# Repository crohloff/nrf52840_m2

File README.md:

# nrf52840_m2
nrf52840 based M.2 b-key module

## dimensions
- 22mm x 30mm

## features
- m.2 2230 b-key form factor board
- dedicated smd chip antenna for bt
- U.fl connector for NFC antenna
- TC2030 debug connector
- RGB led
- power path management (USB or battery connected)
- battery charging circuit 500mA charging current
- up to 24 free programmable GPIOs(4 analog) without expensive uVias

## board front

## board back

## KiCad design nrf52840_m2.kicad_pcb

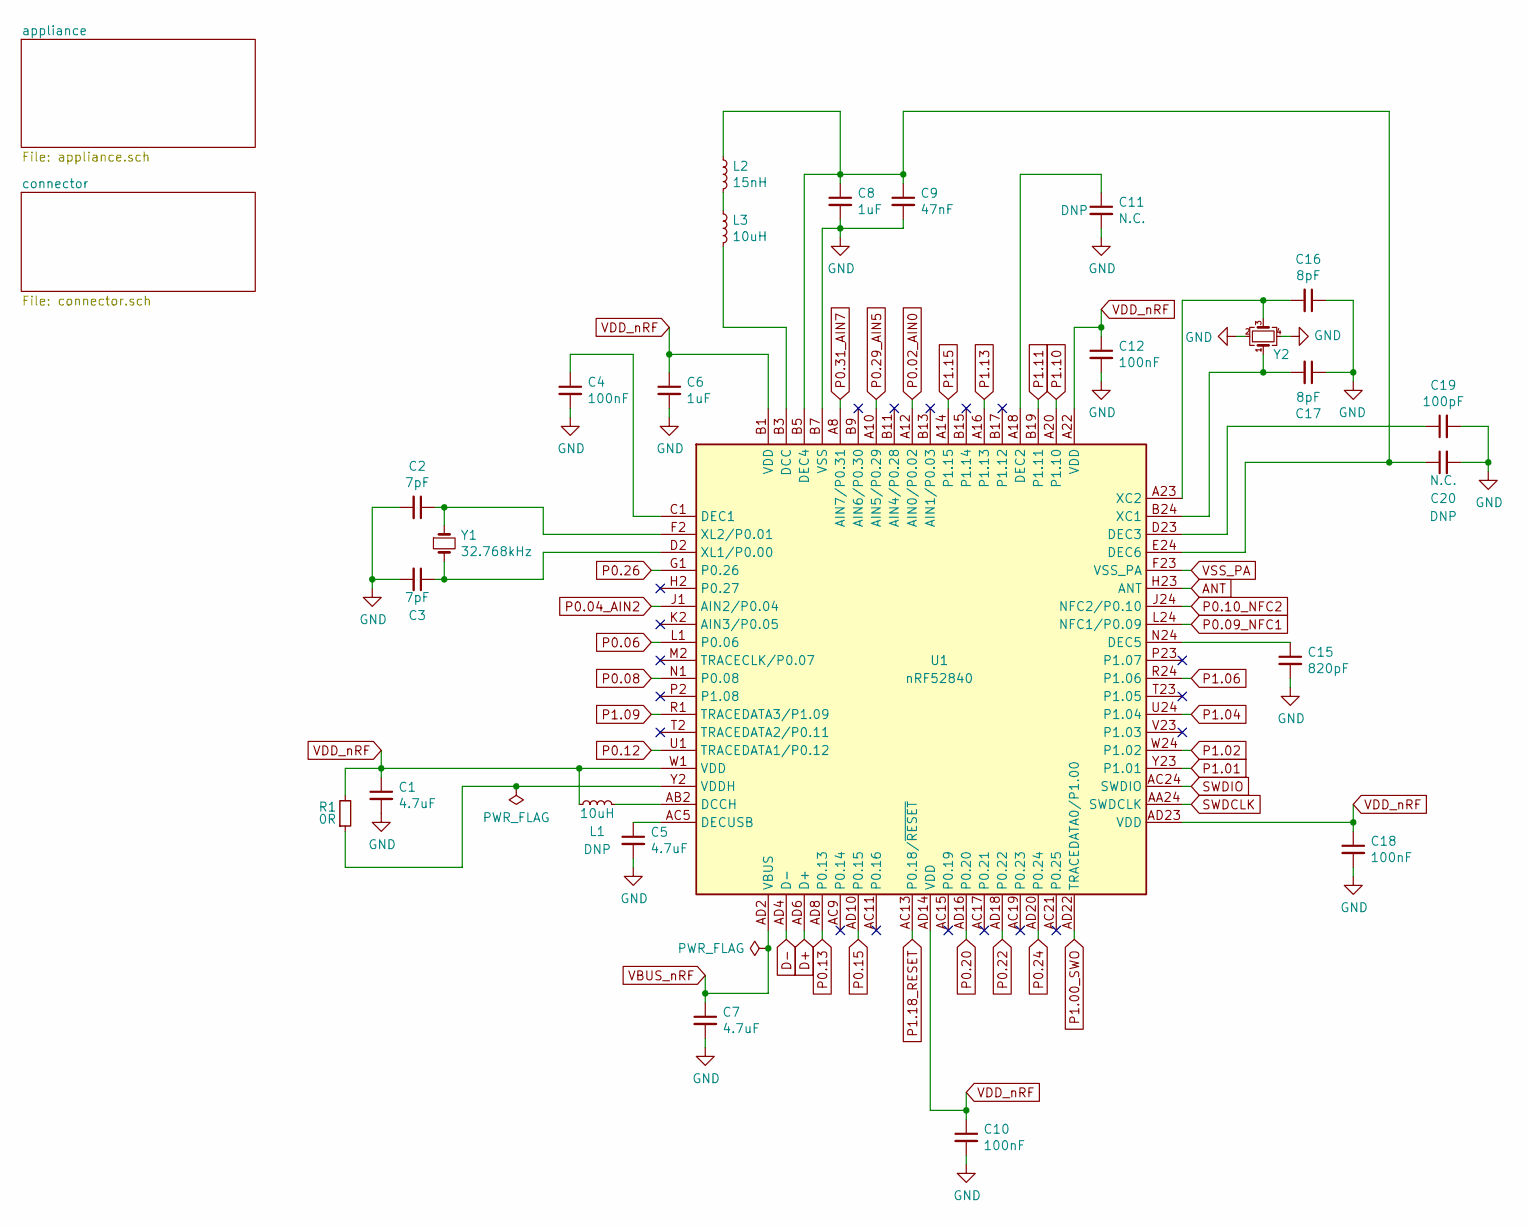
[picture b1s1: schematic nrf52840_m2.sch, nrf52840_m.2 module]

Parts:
C1, C5, C7: 4.7uF; C_0402_1005Metric; MFG P/N JMK105BBJ475MV-F; Digikey 587-2787-1-ND
C2, C3: 7pF; C_0402_1005Metric; MFG P/N GRM1555C1H7R0BA01D; Digikey 490-6254-1-ND
C4, C10, C12, C18: 100nF; C_0402_1005Metric; MFG P/N CL05A104KP5NNNC; Digikey 1276-1022-1-ND
C6, C8: 1uF; C_0402_1005Metric; MFG P/N CL05A105KO5NNNC; Digikey 1276-1067-1-ND
C9: 47nF; C_0402_1005Metric; MFG P/N CC0402KRX7R9BB473; Digikey 311-3815-1-ND
C11, C20: N.C.; C_0402_1005Metric
C15: 820pF; C_0402_1005Metric; MFG P/N CL05B821KB5NNNC; Digikey 1276-1589-1-ND
C16, C17: 8pF; C_0402_1005Metric; MFG P/N CC0402CRNPO9BN8R0; Digikey 311-3328-1-ND
C19: 100pF; C_0402_1005Metric; MFG P/N CC0402JRNPO9BN101; Digikey 311-1024-1-ND
L1, L3: 10uH; L_0603_1608Metric; MFG P/N LQM18FN100M00D; Digikey 490-4025-1-ND
L2: 15nH; L_0402_1005Metric; MFG P/N LQW15AN15NG00D; Digikey 490-6771-1-ND
R1: 0R; R_0402_1005Metric; MFG P/N RC0402JR-070RL; Digikey 311-0.0JRCT-ND
U1: nRF52840; Nordic_AQFN-73-1EP_7x7mm_P0.5mm; MFG P/N NRF52840-QIAA-R; Digikey 1490-1071-1-ND
Y1: 32.768kHz; Crystal_SMD_2012-2Pin_2.0x1.2mm; MFG P/N SC20S-7PF20PPM; Digikey 728-1076-1-ND
Y2: 32MHz; Crystal_SMD_2016-4Pin_2.0x1.6mm; MFG P/N X201632MKD4SI; LCSC C108165

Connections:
ANT: U1.H23 (ANT); also elsewhere on the board
D+: U1.AD6 (D+); also elsewhere on the board
D-: U1.AD4 (D-); also elsewhere on the board
unnamed: C2.1, U1.F2 (XL2/P0.01), Y1.1
unnamed: C3.1, U1.D2 (XL1/P0.00), Y1.2
unnamed: C4.1, U1.C1 (DEC1)
unnamed: C5.1, U1.AC5 (DECUSB)
unnamed: C11.1, U1.A18 (DEC2)
unnamed: C15.1, U1.N24 (DEC5)
unnamed: C16.2, U1.A23 (XC2), Y2.3
unnamed: C17.2, U1.B24 (XC1), Y2.1
unnamed: C19.1, U1.D23 (DEC3)
unnamed: C8.1, C9.1, C20.1, L2.1, U1.B5 (DEC4), U1.E24 (DEC6)
unnamed: L1.2, U1.AB2 (DCCH)
unnamed: L2.2, L3.1
unnamed: L3.2, U1.B3 (DCC)
unnamed: R1.1, U1.Y2 (VDDH)
P0.02_AIN0: U1.A12 (AIN0/P0.02); also elsewhere on the board
P0.04_AIN2: U1.J1 (AIN2/P0.04); also elsewhere on the board
P0.06: U1.L1 (P0.06); also elsewhere on the board
P0.08: U1.N1 (P0.08); also elsewhere on the board
P0.09_NFC1: U1.L24 (NFC1/P0.09); also elsewhere on the board
P0.10_NFC2: U1.J24 (NFC2/P0.10); also elsewhere on the board
P0.12: U1.U1 (TRACEDATA1/P0.12); also elsewhere on the board
P0.13: U1.AD8 (P0.13); also elsewhere on the board
P0.15: U1.AD10 (P0.15); also elsewhere on the board
P0.20: U1.AD16 (P0.20); also elsewhere on the board
P0.22: U1.AD18 (P0.22); also elsewhere on the board
P0.24: U1.AD20 (P0.24); also elsewhere on the board
P0.26: U1.G1 (P0.26); also elsewhere on the board
P0.29_AIN5: U1.A10 (AIN5/P0.29); also elsewhere on the board
P0.31_AIN7: U1.A8 (AIN7/P0.31); also elsewhere on the board
P1.00_SWO: U1.AD22 (TRACEDATA0/P1.00); also elsewhere on the board
P1.01: U1.Y23 (P1.01); also elsewhere on the board
P1.02: U1.W24 (P1.02); also elsewhere on the board
P1.04: U1.U24 (P1.04); also elsewhere on the board
P1.06: U1.R24 (P1.06); also elsewhere on the board
P1.09: U1.R1 (TRACEDATA3/P1.09); also elsewhere on the board
P1.10: U1.A20 (P1.10); also elsewhere on the board
P1.11: U1.B19 (P1.11); also elsewhere on the board
P1.13: U1.A16 (P1.13); also elsewhere on the board
P1.15: U1.A14 (P1.15); also elsewhere on the board
P1.18_RESET: U1.AC13 (P0.18/~RESET); also elsewhere on the board
SWDCLK: U1.AA24 (SWDCLK); also elsewhere on the board
SWDIO: U1.AC24 (SWDIO); also elsewhere on the board
VBUS_nRF: C7.1, U1.AD2 (VBUS); also elsewhere on the board
VDD_nRF: C1.1, C6.1, C10.1, C12.1, C18.1, L1.1, R1.2, U1.A22 (VDD), U1.AD14 (VDD), U1.AD23 (VDD), U1.B1 (VDD), U1.W1 (VDD); also elsewhere on the board
VSS_PA: C1.2, C2.2, C3.2, C4.2, C5.2, C6.2, C7.2, C8.2, C9.2, C10.2, C11.2, C12.2, C15.2, C16.1, C17.1, C18.2, C19.2, C20.2, U1.B7 (VSS), U1.EP (VSS), U1.F23 (VSS_PA), Y2.2, Y2.4; also elsewhere on the board

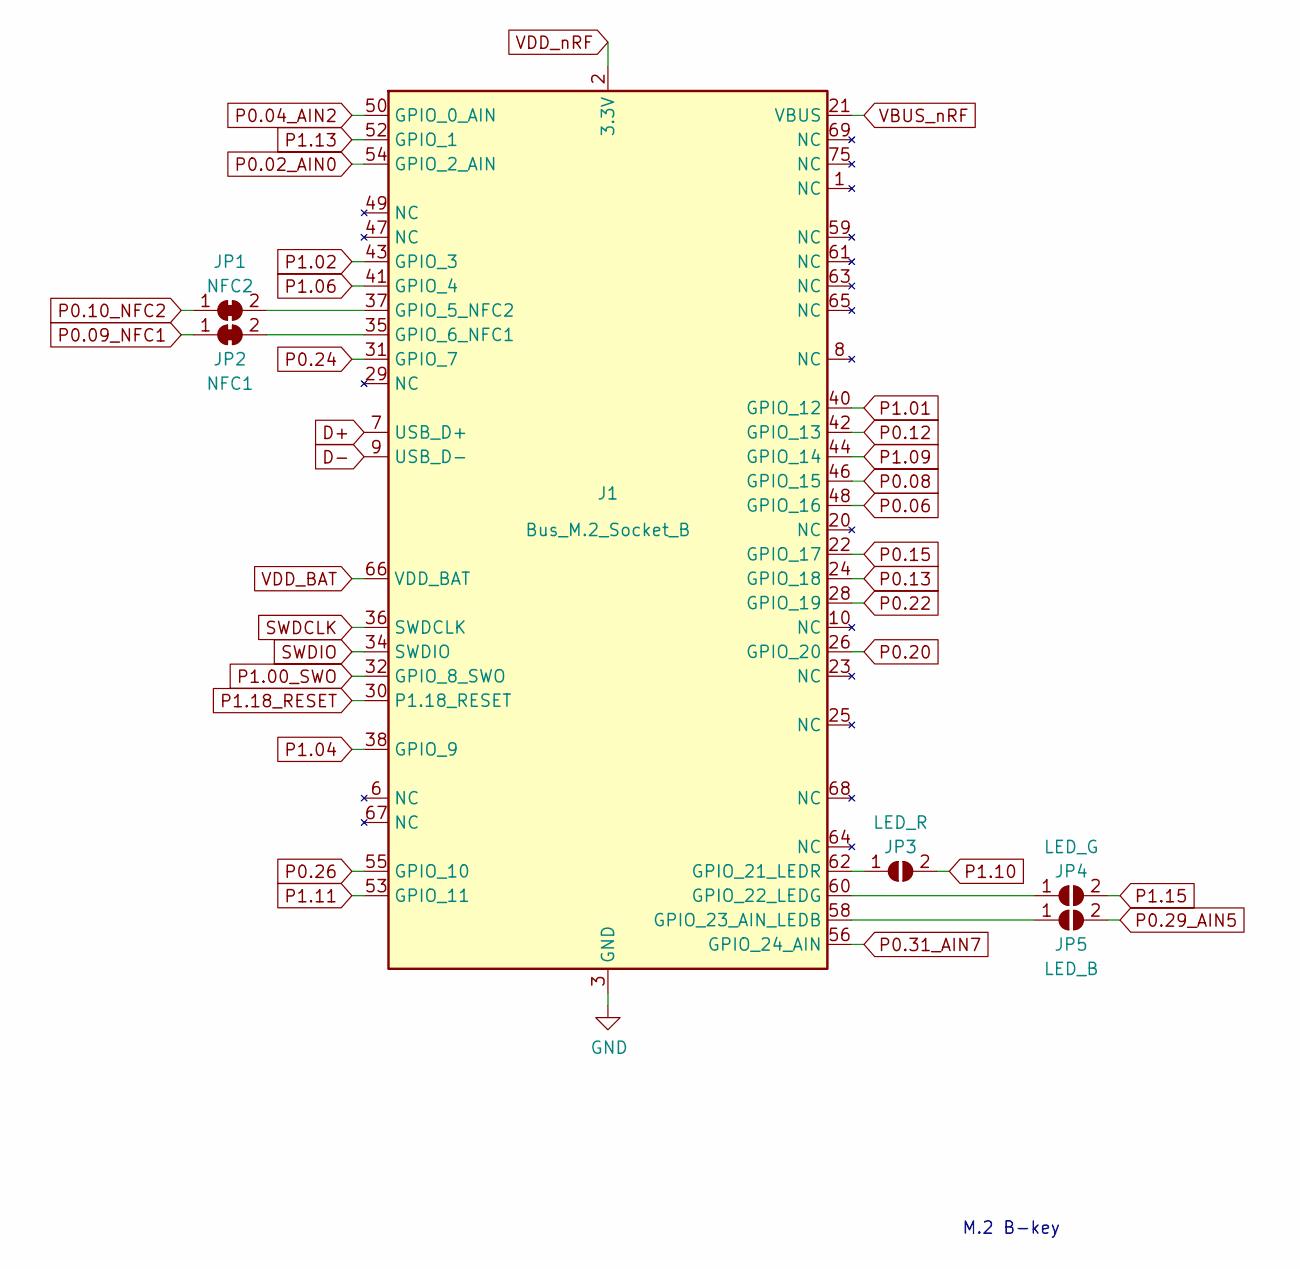
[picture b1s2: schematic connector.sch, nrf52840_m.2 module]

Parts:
J1: Bus_M.2_Socket_B; NGFF_B
JP1: NFC2; solder_bridge_closed
JP2: NFC1; solder_bridge_closed
JP3: LED_R; solder_bridge_open
JP4: LED_G; solder_bridge_open
JP5: LED_B; solder_bridge_open

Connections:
D+: J1.7 (USB_D+); also elsewhere on the board
D-: J1.9 (USB_D-); also elsewhere on the board
unnamed: J1.35 (GPIO_6_NFC1), JP2.2 (B)
unnamed: J1.37 (GPIO_5_NFC2), JP1.2 (B)
unnamed: J1.58 (GPIO_23_AIN_LEDB), JP5.1 (A)
unnamed: J1.60 (GPIO_22_LEDG), JP4.1 (A)
unnamed: J1.62 (GPIO_21_LEDR), JP3.1 (A)
P0.02_AIN0: J1.54 (GPIO_2_AIN); also elsewhere on the board
P0.04_AIN2: J1.50 (GPIO_0_AIN); also elsewhere on the board
P0.06: J1.48 (GPIO_16); also elsewhere on the board
P0.08: J1.46 (GPIO_15); also elsewhere on the board
P0.09_NFC1: JP2.1 (A); also elsewhere on the board
P0.10_NFC2: JP1.1 (A); also elsewhere on the board
P0.12: J1.42 (GPIO_13); also elsewhere on the board
P0.13: J1.24 (GPIO_18); also elsewhere on the board
P0.15: J1.22 (GPIO_17); also elsewhere on the board
P0.20: J1.26 (GPIO_20); also elsewhere on the board
P0.22: J1.28 (GPIO_19); also elsewhere on the board
P0.24: J1.31 (GPIO_7); also elsewhere on the board
P0.26: J1.55 (GPIO_10); also elsewhere on the board
P0.29_AIN5: JP5.2 (B); also elsewhere on the board
P0.31_AIN7: J1.56 (GPIO_24_AIN); also elsewhere on the board
P1.00_SWO: J1.32 (GPIO_8_SWO); also elsewhere on the board
P1.01: J1.40 (GPIO_12); also elsewhere on the board
P1.02: J1.43 (GPIO_3); also elsewhere on the board
P1.04: J1.38 (GPIO_9); also elsewhere on the board
P1.06: J1.41 (GPIO_4); also elsewhere on the board
P1.09: J1.44 (GPIO_14); also elsewhere on the board
P1.10: JP3.2 (B); also elsewhere on the board
P1.11: J1.53 (GPIO_11); also elsewhere on the board
P1.13: J1.52 (GPIO_1); also elsewhere on the board
P1.15: JP4.2 (B); also elsewhere on the board
P1.18_RESET: J1.30 (P1.18_RESET); also elsewhere on the board
SWDCLK: J1.36 (SWDCLK); also elsewhere on the board
SWDIO: J1.34 (SWDIO); also elsewhere on the board
VBUS_nRF: J1.21 (VBUS); also elsewhere on the board
VDD_BAT: J1.66 (VDD_BAT); also elsewhere on the board
VDD_nRF: J1.2 (3.3V), J1.4 (3.3V), J1.70 (3.3V), J1.72 (3.3V), J1.74 (3.3V); also elsewhere on the board
VSS_PA: J1.3 (GND), J1.5 (GND), J1.11 (GND), J1.27 (GND), J1.33 (GND), J1.39 (GND), J1.45 (GND), J1.51 (GND), J1.57 (GND), J1.71 (GND), J1.73 (GND); also elsewhere on the board

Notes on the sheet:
M.2 B-key

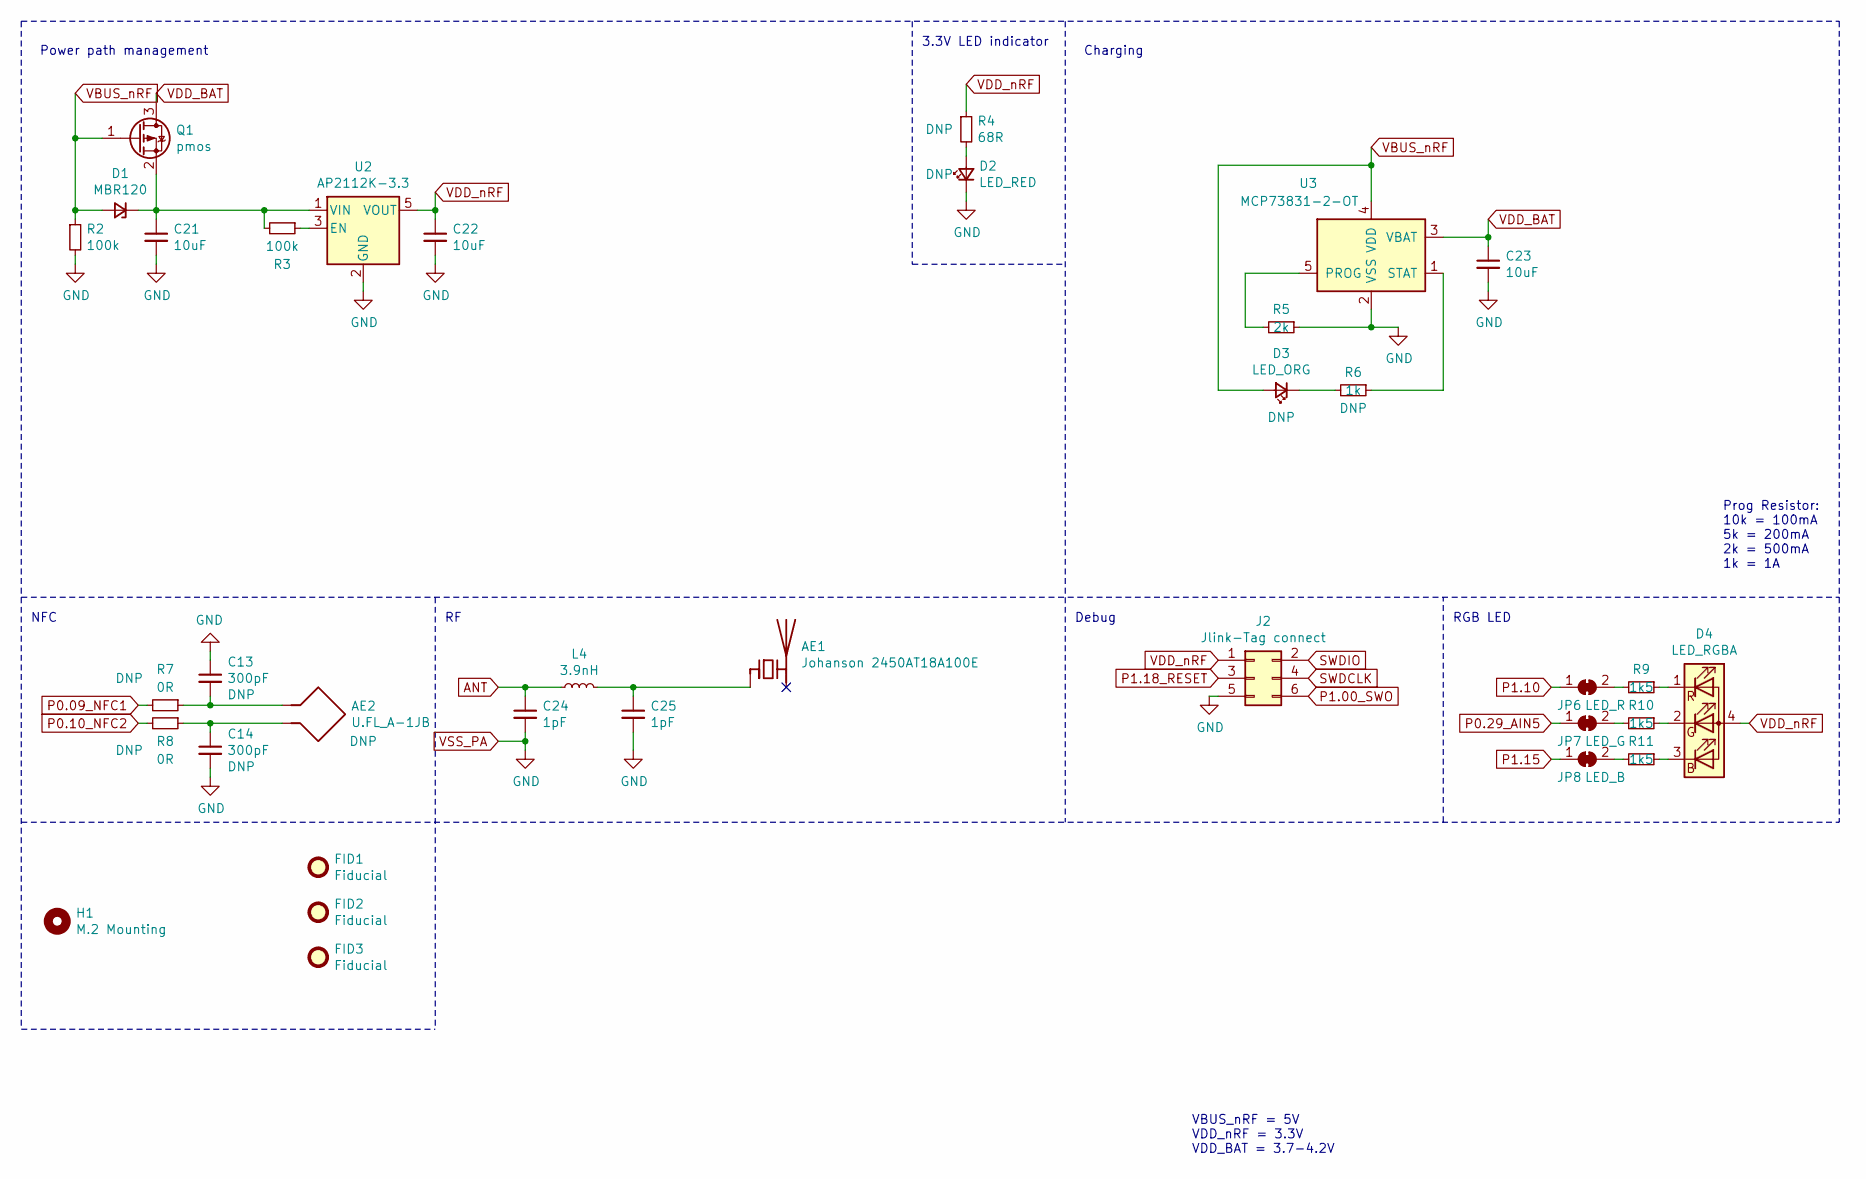
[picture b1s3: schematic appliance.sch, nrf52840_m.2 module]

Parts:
AE1: Johanson 2450AT18A100E; Johanson_2450AT18x100; MFG P/N 2450AT18A100E; Digikey 712-1005-1-ND
AE2: U.FL_A-1JB; CON_AMP_A-1JB; MFG P/N A-1JB; Digikey ARF1579CT-ND
C13, C14: 300pF; C_0402_1005Metric
C21, C22, C23: 10uF; C_0402_1005Metric; MFG P/N CL05A106MQ5NUNC; Digikey 1276-1451-1-ND
C24, C25: 1pF; C_0402_1005Metric; MFG P/N CC0402CRNPO9BN1R0; Digikey 311-2076-1-ND
D1: MBR120; D_SOD-123; MFG P/N MBR120VLSFT1G; Digikey MBR120VLSFT1GOSCT-ND
D2: LED_RED; LED_0603_1608Metric; MFG P/N LTST-C191KRKT; Digikey 160-1447-1-ND
D3: LED_ORG; LED_0603_1608Metric; MFG P/N LTST-C190KFKT; Digikey 160-1434-1-ND
D4: LED_RGBA; LED_LiteOn_LTST-C19HE1WT; MFG P/N LTST-C19HE1WT; Digikey 160-2162-1-ND
FID1, FID2, FID3: Fiducial; Fiducial_0.5mm_Mask1mm
H1: M.2 Mounting; MountingHole_3.2mm_M3
J2: Jlink-Tag connect; Tag-Connect_TC2030-IDC-NL_2x03_P1.27mm_Vertical
JP6: LED_R; solder_bridge_closed
JP7: LED_G; solder_bridge_closed
JP8: LED_B; solder_bridge_closed
L4: 3.9nH; L_0402_1005Metric; MFG P/N LQG15HN3N9S02D; Digikey 490-1079-1-ND
Q1: pmos; SOT-23; MFG P/N NTR1P02T1G; Digikey NTR1P02T1GOSTR-ND
R2, R3: 100k; R_0402_1005Metric; MFG P/N RC0402JR-07100KL; Digikey 311-100KJRCT-ND
R4: 68R; R_0402_1005Metric; MFG P/N AC0402FR-0768RL; Digikey YAG3507CT-ND
R5: 2k; R_0402_1005Metric; MFG P/N RC0402FR-072KL; Digikey 311-2KLRCT-ND
R6: 1k; R_0402_1005Metric; MFG P/N RC0402JR-071KL; Digikey 311-1.0KJRCT-ND
R7, R8: 0R; R_0402_1005Metric
R9, R10, R11: 1k5; R_0402_1005Metric; MFG P/N RC0402FR-071K5L; Digikey 311-1.50KLRCT-ND
U2: AP2112K-3.3; SOT-23-5; MFG P/N AP2112K-3.3TRG1; Digikey AP2112K-3.3TRG1DICT-ND
U3: MCP73831-2-OT; SOT-23-5; MFG P/N MCP73831T-2ATI/OT; Digikey MCP73831T-2ATI/OTCT-ND

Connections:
ANT: C24.1, L4.1; also elsewhere on the board
unnamed 3: AE1.1 (FEED), C25.1, L4.2; also elsewhere on the board
unnamed 5: AE2.1, C13.2, R7.1; also elsewhere on the board
unnamed 6: AE2.2, C14.1, R8.1; also elsewhere on the board
unnamed: C21.1, D1.1 (K), Q1.2 (S), R3.2, U2.1 (VIN)
unnamed: D2.2 (A), R4.2
unnamed: D3.1 (K), R6.2
unnamed: D4.1 (RK), R9.1
unnamed: D4.2 (GK), R10.1
unnamed: D4.3 (BK), R11.1
unnamed: JP6.2 (B), R9.2
unnamed: JP7.2 (B), R10.2
unnamed: JP8.2 (B), R11.2
unnamed: R3.1, U2.3 (EN)
unnamed: R5.2, U3.5 (PROG)
unnamed: R6.1, U3.1 (STAT)
P0.09_NFC1: R7.2; also elsewhere on the board
P0.10_NFC2: R8.2; also elsewhere on the board
P0.29_AIN5: JP7.1 (A); also elsewhere on the board
P1.00_SWO: J2.6; also elsewhere on the board
P1.10: JP6.1 (A); also elsewhere on the board
P1.15: JP8.1 (A); also elsewhere on the board
P1.18_RESET: J2.3; also elsewhere on the board
SWDCLK: J2.4; also elsewhere on the board
SWDIO: J2.2; also elsewhere on the board
VBUS_nRF: D1.2 (A), D3.2 (A), Q1.1 (G), R2.1, U3.4 (VDD); also elsewhere on the board
VDD_BAT: C23.1, Q1.3 (D), U3.3 (VBAT); also elsewhere on the board
VDD_nRF: C22.1, D4.4 (A), J2.1, R4.1, U2.5 (VOUT); also elsewhere on the board
VSS_PA: C13.1, C14.2, C21.2, C22.2, C23.2, C24.2, C25.2, D2.1 (K), J2.5, R2.2, R5.1, U2.2 (GND), U3.2 (VSS); also elsewhere on the board

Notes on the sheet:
VBUS_nRF = 5V VDD_nRF = 3.3V VDD_BAT = 3.7-4.2V
Power path management
Prog Resistor: 10k = 100mA 5k = 200mA 2k = 500mA 1k = 1A
Charging
NFC
Debug
3.3V LED indicator
RGB LED

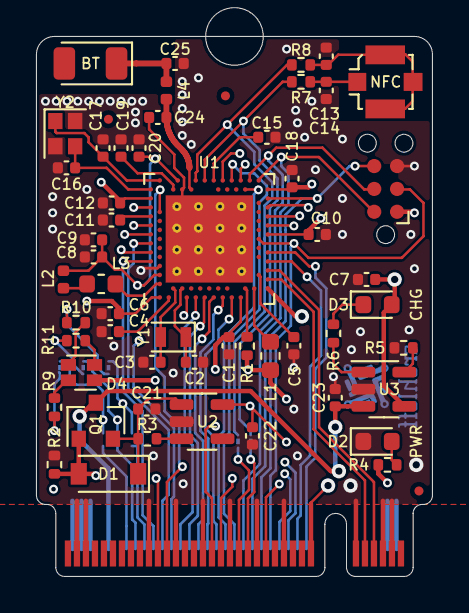
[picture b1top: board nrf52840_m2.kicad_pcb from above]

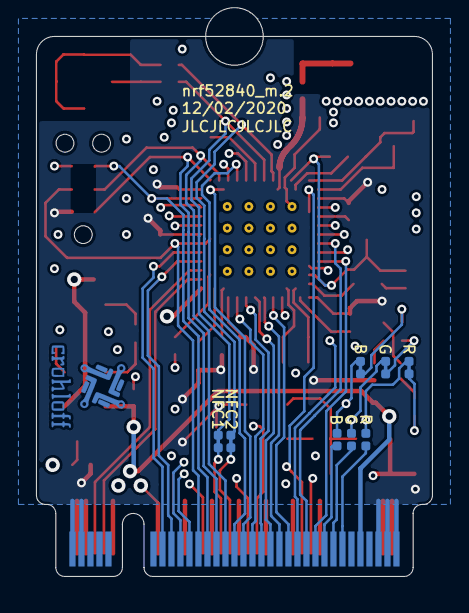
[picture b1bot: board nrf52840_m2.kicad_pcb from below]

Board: 4 copper layers, 22.0 x 30.0 mm, 66 parts (8 on the bottom side), 69 nets.

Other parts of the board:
BT: Johanson 2450AT18A100E; Johanson_2450AT18x100
NFC: U.FL_A-1JB; CON_AMP_A-1JB

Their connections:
unnamed 3: BT.1; also elsewhere on the board
unnamed 5: NFC.1; also elsewhere on the board
unnamed 6: NFC.2; also elsewhere on the board

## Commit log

2020-12-02 initial setup
2021-01-20 update 3D/docs/fiducials
2021-01-20 update files
2021-05-13 adjust m.2 mounting diameter
